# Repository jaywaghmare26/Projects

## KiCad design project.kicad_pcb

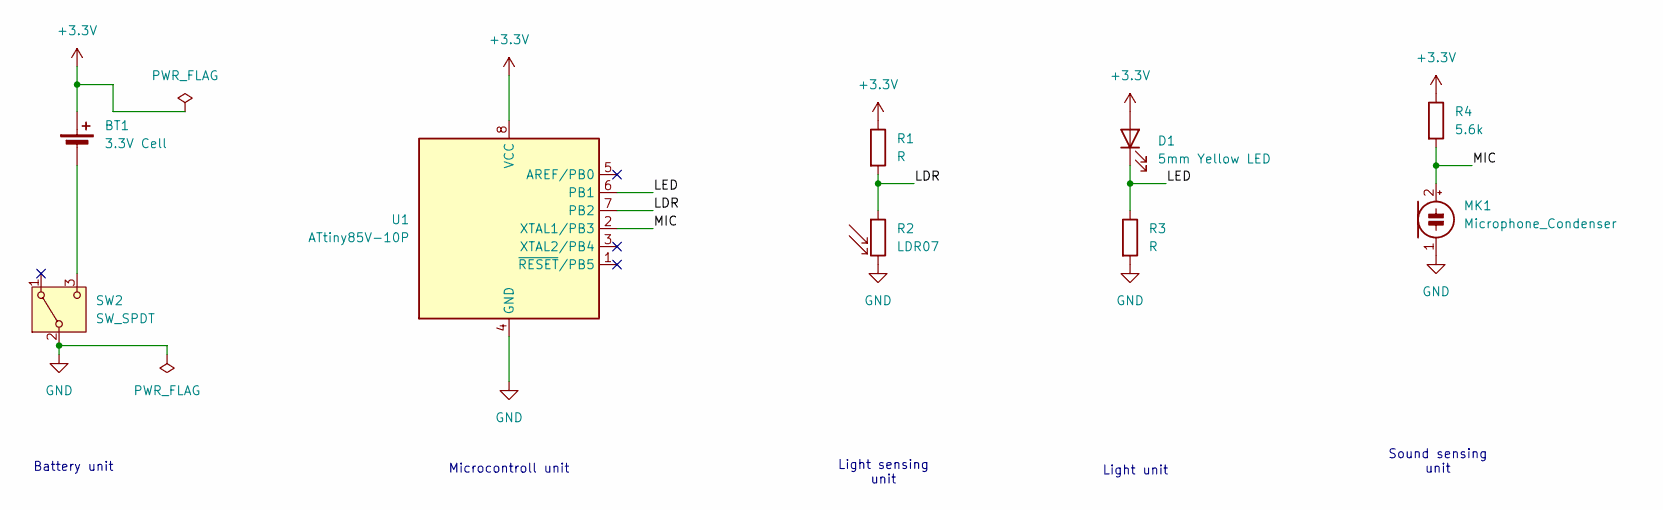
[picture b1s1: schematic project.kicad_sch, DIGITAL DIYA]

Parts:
BT1: 3.3V Cell; BatteryHolder_ComfortableElectronic_CH273-2450_1x2450
D1: 5mm Yellow LED; LED_D5.0mm
MK1: Microphone_Condenser; PinSocket_1x02_P2.54mm_Vertical
R1, R3: R; R_Axial_DIN0207_L6.3mm_D2.5mm_P15.24mm_Horizontal
R2: LDR07; R_LDR_5.1x4.3mm_P3.4mm_Vertical
R4: 5.6k; R_Axial_DIN0207_L6.3mm_D2.5mm_P15.24mm_Horizontal
SW2: SW_SPDT; SW_E-Switch_EG1224_SPDT_Angled
U1: ATtiny85V-10P; DIP-8_W7.62mm

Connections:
+3.3V: BT1.1 (+), D1.2 (A), R1.1, R4.1, U1.8 (VCC)
/LDR: R1.2, R2.1, U1.7 (PB2)
/LED: D1.1 (K), R3.1, U1.6 (PB1)
/MIC: MK1.2 (+), R4.2, U1.2 (XTAL1/PB3)
GND: MK1.1 (-), R2.2, R3.2, SW2.2 (B), U1.4 (GND)
unnamed: BT1.2 (-), SW2.3 (C)

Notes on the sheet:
Battery unit
Sound sensing unit
Light unit
Microcontroll unit
Light sensing unit

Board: 2 copper layers, 9 parts (0 on the bottom side), 6 nets, no tracks yet.

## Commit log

2026-01-11 Create digital diya
